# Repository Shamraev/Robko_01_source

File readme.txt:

Исходники для разработки программной части системы упрпавления
для робота "Робко 01" с 5 степенями свободы
Шамраев А.Д. 2019/2020
плейлист видео: (https://youtube.com/playlist?list=PLJ-_6HNRnl0PleVZsJ_78o03qlgVmuRIi)
*********************************************************************************
В каждой нижеперечисленной папке находятся пояснения в файле 'readme.txt'

В 'Programm' находятся исходники для десктопного приложения (для ПК)
среда разработки - Visual Studio C# 2017

В 'Robko_firmware' находятся исходники для прошивки микроконтроллера (для МК)
среда разработки - Visual Studio Code v.1.4 с дополнениями Arduino, C++; 
загрузка в МК с помощью Arduino IDE 1.8.5

В 'robko_PCB_arduino_shield' находятся исходники для проектирования платы управления
среда разработки - KiCad v.5.1.0

В 'Robko_workspase' находятся исходники для расчета операционного пространства
среда разработки - Matlab R2016a

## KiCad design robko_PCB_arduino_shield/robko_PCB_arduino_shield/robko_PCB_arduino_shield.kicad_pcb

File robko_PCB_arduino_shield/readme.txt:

Плата управления для робота "Робко 01" с 5 степенями свободы
Разработано в KiCad v.5.1.0
Шамраев А.Д. 2019
**********************************************************
По своей сути эта плата - есть аналог Ramps 1.4 shield.
Она соединает микроконтроллер (Arduino mega 2560),
драйверы (A4988) и шаговые двигатели (в "Робко 01")

Комплектующие:
A4988                                     - 6 штук
Arduino mega 2560                  - 1 штука
кондексатор 50 В, 100 мкФ    - 6 штук
резистор 10 кОм                    - 6 штук

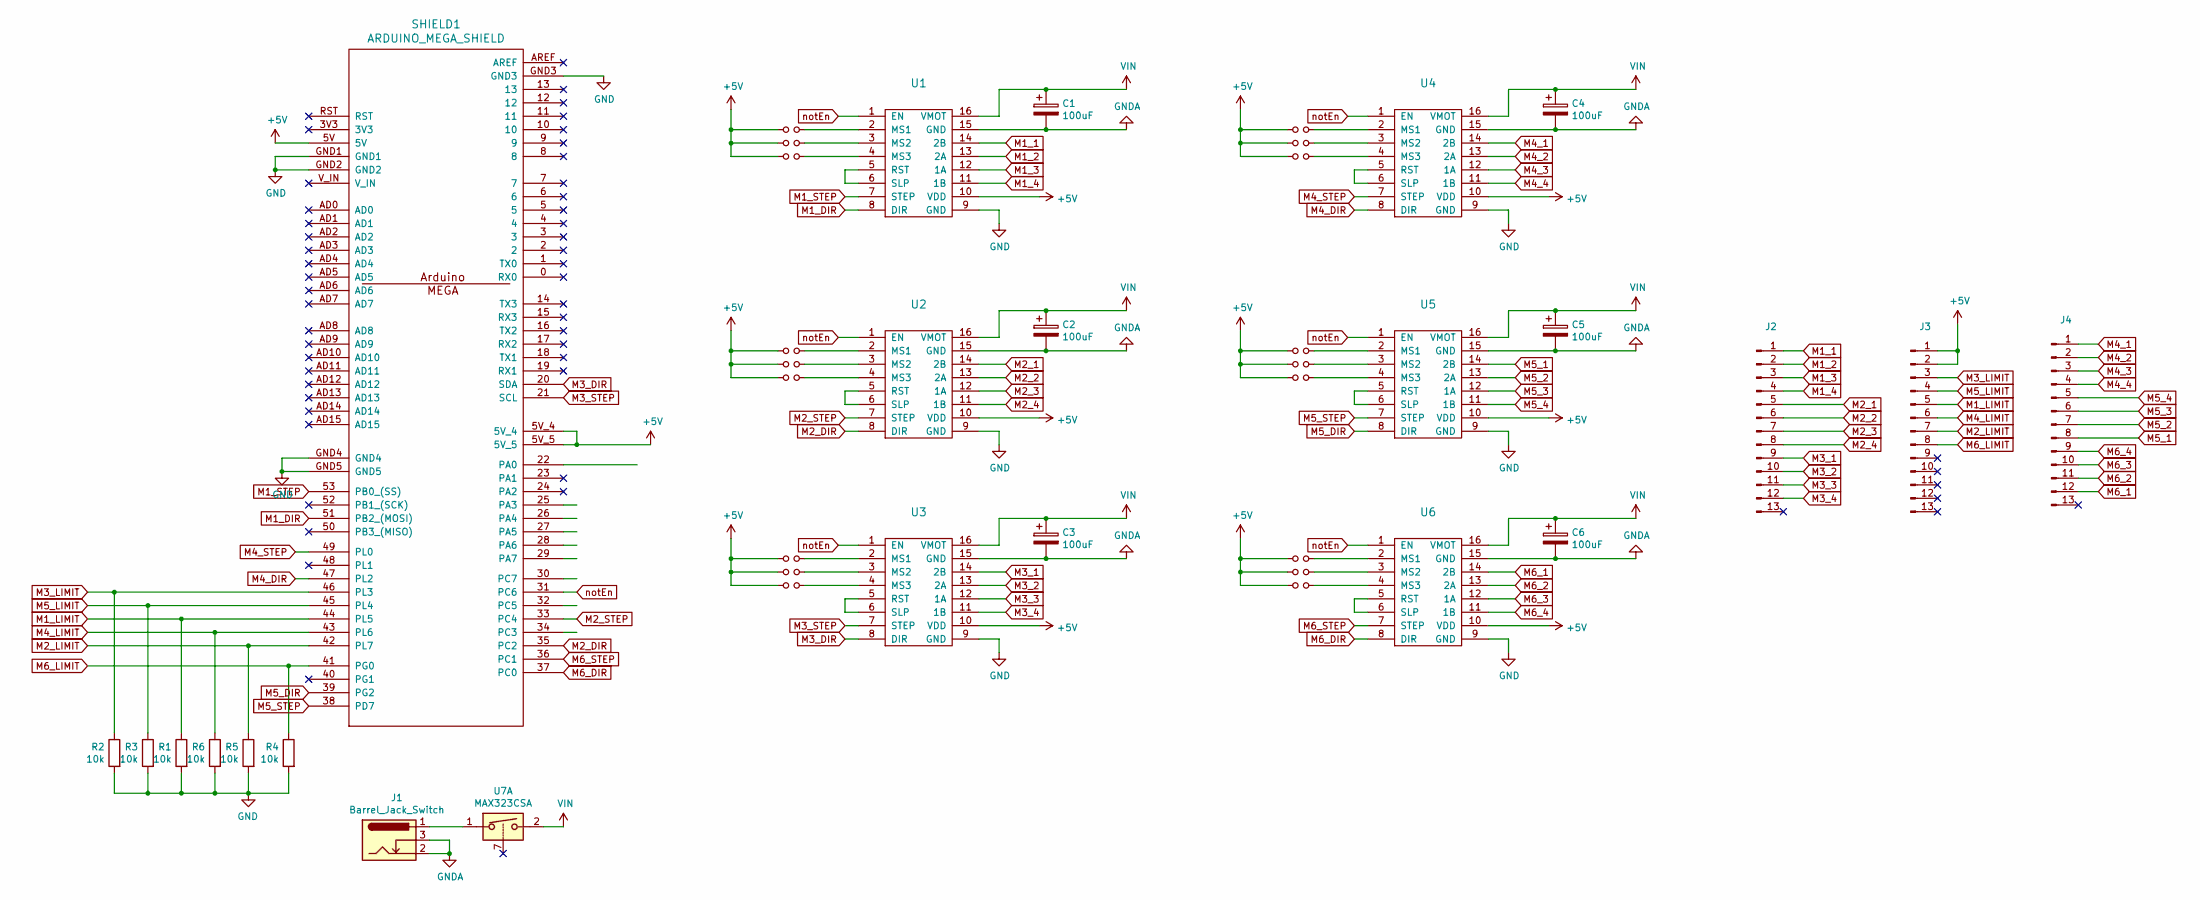
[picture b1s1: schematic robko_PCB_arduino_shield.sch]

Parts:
C1, C2, C3, C4, C5, C6: 100uF; CP_Radial_D10.0mm_P3.50mm
J1: Barrel_Jack_Switch; BarrelJack_CUI_PJ-102AH_Horizontal
J2, J3, J4: Conn_01x13_Male; PinHeader_1x13_P2.54mm_Vertical
JP1, JP2, JP3, JP4, JP5, JP6, JP7, JP8, JP9, JP10, JP11, JP12, JP13, JP14, JP15, JP16, JP17, JP18: Jumper_NO_Small; PinHeader_1x02_P2.54mm_Vertical
R1, R2, R3, R4, R5, R6: 10k; R_Axial_DIN0207_L6.3mm_D2.5mm_P7.62mm_Horizontal
SHIELD1: ARDUINO_MEGA_SHIELD
U1, U2, U3, U4, U5, U6: POLOLU_STEPPER_DRIVER; a4988_shield
U7: MAX323CSA; switch_13

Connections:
+5V: J3.1, J3.2, JP1.1, JP2.1, JP3.1, JP4.1, JP5.1, JP6.1, JP7.1, JP8.1, JP9.1, JP10.1, JP11.1, JP12.1, JP13.1, JP14.1, JP15.1, JP16.1, JP17.1, JP18.1, SHIELD1.5V, SHIELD1.5V_4, SHIELD1.5V_5, U1.10 (VDD), U2.10 (VDD), U3.10 (VDD), U4.10 (VDD), U5.10 (VDD), U6.10 (VDD)
GND: R1.2, R2.2, R3.2, R4.2, R5.2, R6.2, SHIELD1.GND1, SHIELD1.GND2, SHIELD1.GND3, SHIELD1.GND4, SHIELD1.GND5, U1.9 (GND), U2.9 (GND), U3.9 (GND), U4.9 (GND), U5.9 (GND), U6.9 (GND)
GNDA: C1.2, C2.2, C3.2, C4.2, C5.2, C6.2, J1.2, J1.3, U1.15 (GND), U2.15 (GND), U3.15 (GND), U4.15 (GND), U5.15 (GND), U6.15 (GND)
M1_1: J2.1, U1.14 (2B)
M1_2: J2.2, U1.13 (2A)
M1_3: J2.3, U1.12 (1A)
M1_4: J2.4, U1.11 (1B)
M1_DIR: SHIELD1.51 (PB2_(MOSI)), U1.8 (DIR)
M1_LIMIT: J3.5, R1.1, SHIELD1.44 (PL5)
M1_STEP: SHIELD1.53 (PB0_(SS)), U1.7 (STEP)
M2_1: J2.5, U2.14 (2B)
M2_2: J2.6, U2.13 (2A)
M2_3: J2.7, U2.12 (1A)
M2_4: J2.8, U2.11 (1B)
M2_DIR: SHIELD1.35 (PC2), U2.8 (DIR)
M2_LIMIT: J3.7, R5.1, SHIELD1.42 (PL7)
M2_STEP: SHIELD1.33 (PC4), U2.7 (STEP)
M3_1: J2.9, U3.14 (2B)
M3_2: J2.10, U3.13 (2A)
M3_3: J2.11, U3.12 (1A)
M3_4: J2.12, U3.11 (1B)
M3_DIR: SHIELD1.20 (SDA), U3.8 (DIR)
M3_LIMIT: J3.3, R2.1, SHIELD1.46 (PL3)
M3_STEP: SHIELD1.21 (SCL), U3.7 (STEP)
M4_1: J4.1, U4.14 (2B)
M4_2: J4.2, U4.13 (2A)
M4_3: J4.3, U4.12 (1A)
M4_4: J4.4, U4.11 (1B)
M4_DIR: SHIELD1.47 (PL2), U4.8 (DIR)
M4_LIMIT: J3.6, R6.1, SHIELD1.43 (PL6)
M4_STEP: SHIELD1.49 (PL0), U4.7 (STEP)
M5_1: J4.8, U5.14 (2B)
M5_2: J4.7, U5.13 (2A)
M5_3: J4.6, U5.12 (1A)
M5_4: J4.5, U5.11 (1B)
M5_DIR: SHIELD1.39 (PG2), U5.8 (DIR)
M5_LIMIT: J3.4, R3.1, SHIELD1.45 (PL4)
M5_STEP: SHIELD1.38 (PD7), U5.7 (STEP)
M6_1: J4.12, U6.14 (2B)
M6_2: J4.11, U6.13 (2A)
M6_3: J4.10, U6.12 (1A)
M6_4: J4.9, U6.11 (1B)
M6_DIR: SHIELD1.37 (PC0), U6.8 (DIR)
M6_LIMIT: J3.8, R4.1, SHIELD1.41 (PG0)
M6_STEP: SHIELD1.36 (PC1), U6.7 (STEP)
unnamed: J1.1, U7.1
unnamed: JP1.2, U1.2 (MS1)
unnamed: JP2.2, U1.3 (MS2)
unnamed: JP3.2, U1.4 (MS3)
unnamed: JP4.2, U2.2 (MS1)
unnamed: JP5.2, U2.3 (MS2)
unnamed: JP6.2, U2.4 (MS3)
unnamed: JP7.2, U3.2 (MS1)
unnamed: JP8.2, U3.3 (MS2)
unnamed: JP9.2, U3.4 (MS3)
unnamed: JP10.2, U4.2 (MS1)
unnamed: JP11.2, U4.3 (MS2)
unnamed: JP12.2, U4.4 (MS3)
unnamed: JP13.2, U5.2 (MS1)
unnamed: JP14.2, U5.3 (MS2)
unnamed: JP15.2, U5.4 (MS3)
unnamed: JP16.2, U6.2 (MS1)
unnamed: JP17.2, U6.3 (MS2)
unnamed: JP18.2, U6.4 (MS3)
unnamed: U1.5 (RST), U1.6 (SLP)
unnamed: U2.5 (RST), U2.6 (SLP)
unnamed: U3.5 (RST), U3.6 (SLP)
unnamed: U4.5 (RST), U4.6 (SLP)
unnamed: U5.5 (RST), U5.6 (SLP)
unnamed: U6.5 (RST), U6.6 (SLP)
VIN: C1.1, C2.1, C3.1, C4.1, C5.1, C6.1, U1.16 (VMOT), U2.16 (VMOT), U3.16 (VMOT), U4.16 (VMOT), U5.16 (VMOT), U6.16 (VMOT), U7.2
notEn: SHIELD1.31 (PC6), U1.1 (EN), U2.1 (EN), U3.1 (EN), U4.1 (EN), U5.1 (EN), U6.1 (EN)

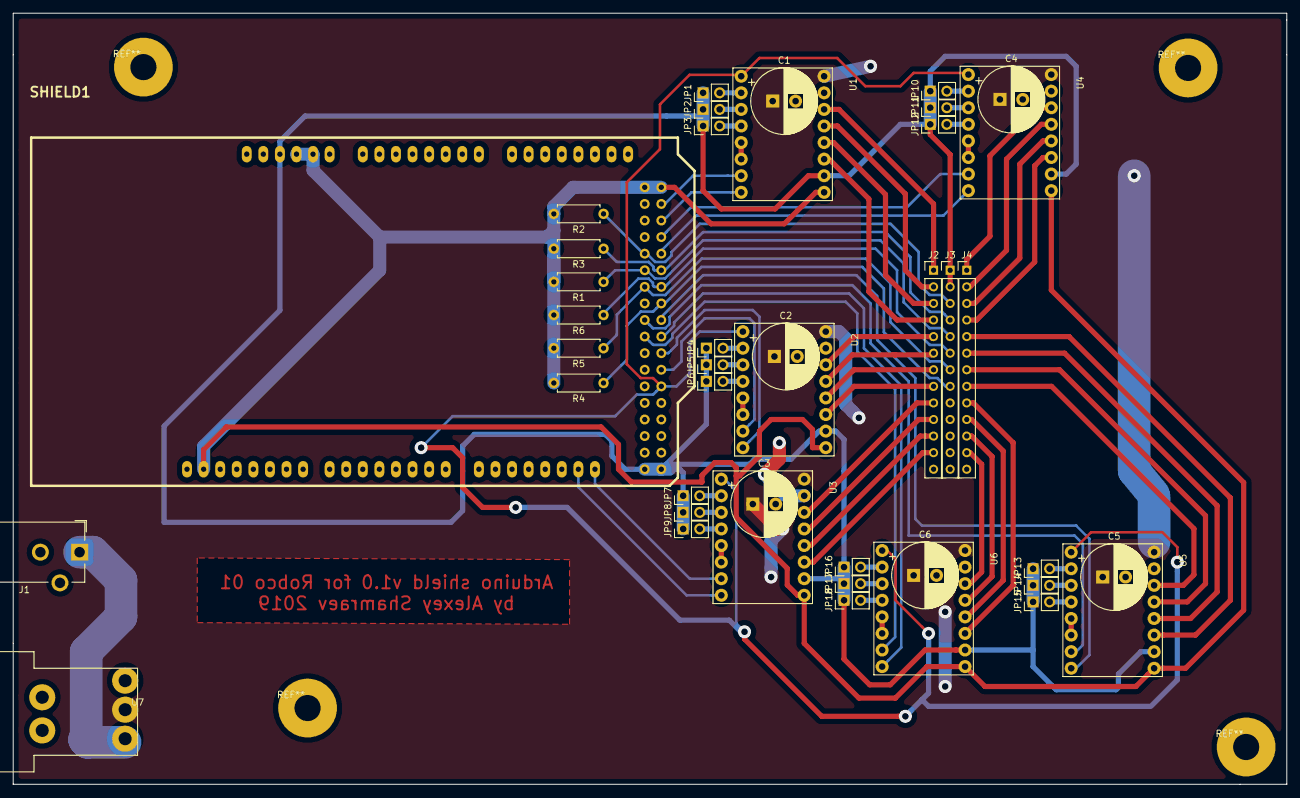
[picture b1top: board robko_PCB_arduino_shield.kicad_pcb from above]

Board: 2 copper layers, 195.1 x 118.1 mm, 42 parts (0 on the bottom side), 72 nets.

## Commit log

2019-12-23 Start
2019-12-25 constant speed
2019-12-30 good moving_0.2_deg
2020-01-07 отправка числе вв виде байтов, проблема - округляет
2020-01-08 передача 3 чисел float из C# в Arduino нормальная
2020-01-08 библиотека ОЗК, решение совпадает с маткадовским; Нужно ввести систему координат в ардиуно и программе
2020-01-08 Проба прямоугольника 50_50; нули совмещены плохо
2020-01-09 IK3DOF IK5DOF; найдены коэффициенты для поправки зажима схвата
2020-01-11 Совмещены нули.
2020-01-24 подключены датчики; нужно вывести функцию нулевое положения; перейти от блокурующего runSpeedToPosition() к run()
2020-01-25 переделано под run; не работает serial.print
2020-03-10 create template lib
2020-03-11 loop
2020-03-17 Выдернули пины на плату в отдельный файл
2020-03-22 раскиданы методы и функции по классу
2020-03-23 PCB_Arduino_shield названы a4998
2020-03-23 исправлены ошибки при компиляции
    исправлены ошибки при компиляции, все необзодимые библиотеки в папке со скетчем
2020-04-03 форматирование; переименование; надписи на роботе, БП
2020-04-04 robko workspace calculation
2020-04-05 параллепипед - область манипулирования шахматами
2020-04-05 приезжает в ноль хорошо, нужно считать сколько шагов сделал
2020-04-06 после срабатывания датчиков возвращается в нули
2020-04-06 Поправлена ошибка (знак '=' вместо '==')
    остается проблема пятого двиагателя - после обнуления слишком много двигается. Скрорость второго двигателя низка при поиске нуля.
2020-04-23 workspace, добавлено описание
2020-04-23 добавлены файлы readme.txt
2020-04-24 улучшен интерфейс десктопного приложения, в прошивку добавлен Debug
2020-04-24 находит нули, возвращается и обнуляется
    нужно сделать: все подзатянуть, настроить скорости, уточнить нули
2020-04-25 уточнены нули
2020-04-25 почищено от мусора, схват работает
2020-04-25 в начале работы прошивки positions_[3] схвата выставляется; добавлена дополнительная форма для текущих координат
2020-04-26 добавлены классы MCControl, CommandSender (начальный этап)
2020-04-26 реализованы команды G00, G01
2020-04-27 МК роботоспособен, ошибка после возвращения в ноли - схват еще дожимает
2020-04-27 проба различных файлов С G кодом
2020-04-28 добавлены комментарии в прошивке
2020-04-28 переход от Arduino IDE к platformIO (плагин для VS Code)
2020-04-30 gitignore debug files
2020-04-30 git remove ignired files from rep
2020-05-02 COM ports good getNames
2020-05-03 Task для выполнения команды в отдельном потоке, G01 работает хорошо
2020-05-03 from Task to Thread in commandSender; Улучшена стабильность работы этого потока
2020-05-03 Пауза даже в исполнении операции g кода, более быстрое соединени с портом
2020-05-03 обработка G команд с точкой
2020-05-03 переименованы функции
2020-05-04 Бибилотека для векторов: операторы +, -, *; функции доступны без упоминания класса
2020-05-04 добавлена структура Cut - отрезок, G01 переделан используя Cut
2020-05-04 переименование проекта
2020-05-04 Вместо структур отрезок, дуга - классы
2020-05-04 после переименования проекта нужно игнорировать файлы отладки
2020-05-05 реализованы команды G02_G03
2020-05-05 G02_G03 не нужно объявлять X Y Z в команде, где полная окружность
2020-05-05 корректировка по Z
2020-05-06 отображение состояния выполнения G кода: текущая строка, итоговое время выполнения; G код файл тест
2020-05-06 РАБОТАЕТ!!! Есть глюки при выполнении ~ 242 строки G кода; mcControl Handler: Reset, Set только при отправке и получении
2020-05-07 GetXYZ_fromStr использует GetNumbers_FromStr
2020-05-07 добавлено логгирование
2020-05-07 повышена надежность при паузе/продолжении цикла; освобождение памяти - сборка мусора
2020-05-07 кнопка старт/пауза
2020-05-08 G код в комментарии
2020-05-09 улучшено логгирование; таймер
2020-05-10 корректирующая плоскость
2020-05-13 Внедрен протокол обмена; исправлена ошибка передачи данных (очистить буфер приема в МК)
2020-05-16 добавлены операции; сжать/разжать схват; обновлен протокол: + STATUS_CODE; обновление статуса операции улучшено;
2020-05-16 tmp: сжать разжать схват: после выполнения операции обнулить двигатель
2020-05-20 Добавлены карты и диаграммы кода в Vidual Studio Enterprise
2020-05-20 SerialPort in MCControl
2020-06-05 git ignore .vdcode file
2020-11-12 trash deleted and CodeMap added
2020-11-20 встроен визуализатор
2020-11-20 обновлено описание, названия папок
2020-11-21 ignore debug files
2020-11-21 удаление вспомогательной- справочной информации по kikad
2020-11-21 garbage cleaning
2020-11-21 ignore all debug and release folders
2020-11-21 ISSUE: appSettings
    создание портабельных настроек. Добавление натсроек окна программы
2021-02-24 correct plane
2021-02-24 visualization
2021-02-24 устранение ошибок симуляции, сохранение текущих координат
2021-02-24 добавление примеров g кодов
2021-02-24 add playlist to readme
2021-02-24 help provider
